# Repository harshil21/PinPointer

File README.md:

View this project on [CADLAB.io](https://cadlab.io/project/29625). 

# PinPointer

This repository will contain all the components which I intend to use for the payload of my rocket. It will include but won't be limited to:

1) Original KiCAD designs for integrating Quectel's LC29H (DA) and (BS) GPS RTK modules
2) Custom Antenna(s) research, building, and tuning, for both GPS and radio telemetry to receive RTCM correction messages from my base station to the rocket.
3) CAD design for assembly of the antennas and modules into the rocket.
4) Microcontroller code (exact microcontroller TBD) which will communicate with an accelerometer (TBD), the GPS module, and a LoRA module (TBD) to transmit and receive at the 915 MHz ISM band.
5) Openrocket file

Primary goals:
1) Scientific curiosity to compare very accurate GPS altitude with pressure altitude.
2) Package and integrate electronics tightly to minimize cost while at the same time have high performance and portability across different rockets. deliberate design decisions.
3) Pave the way for more experimental flights, e.g. active roll control, rocket landings, etc.

Each section will contain how-to's and thought processes. This data will be free and public to everyone who would also like to do the same and iterate.

🚀📡🛰️

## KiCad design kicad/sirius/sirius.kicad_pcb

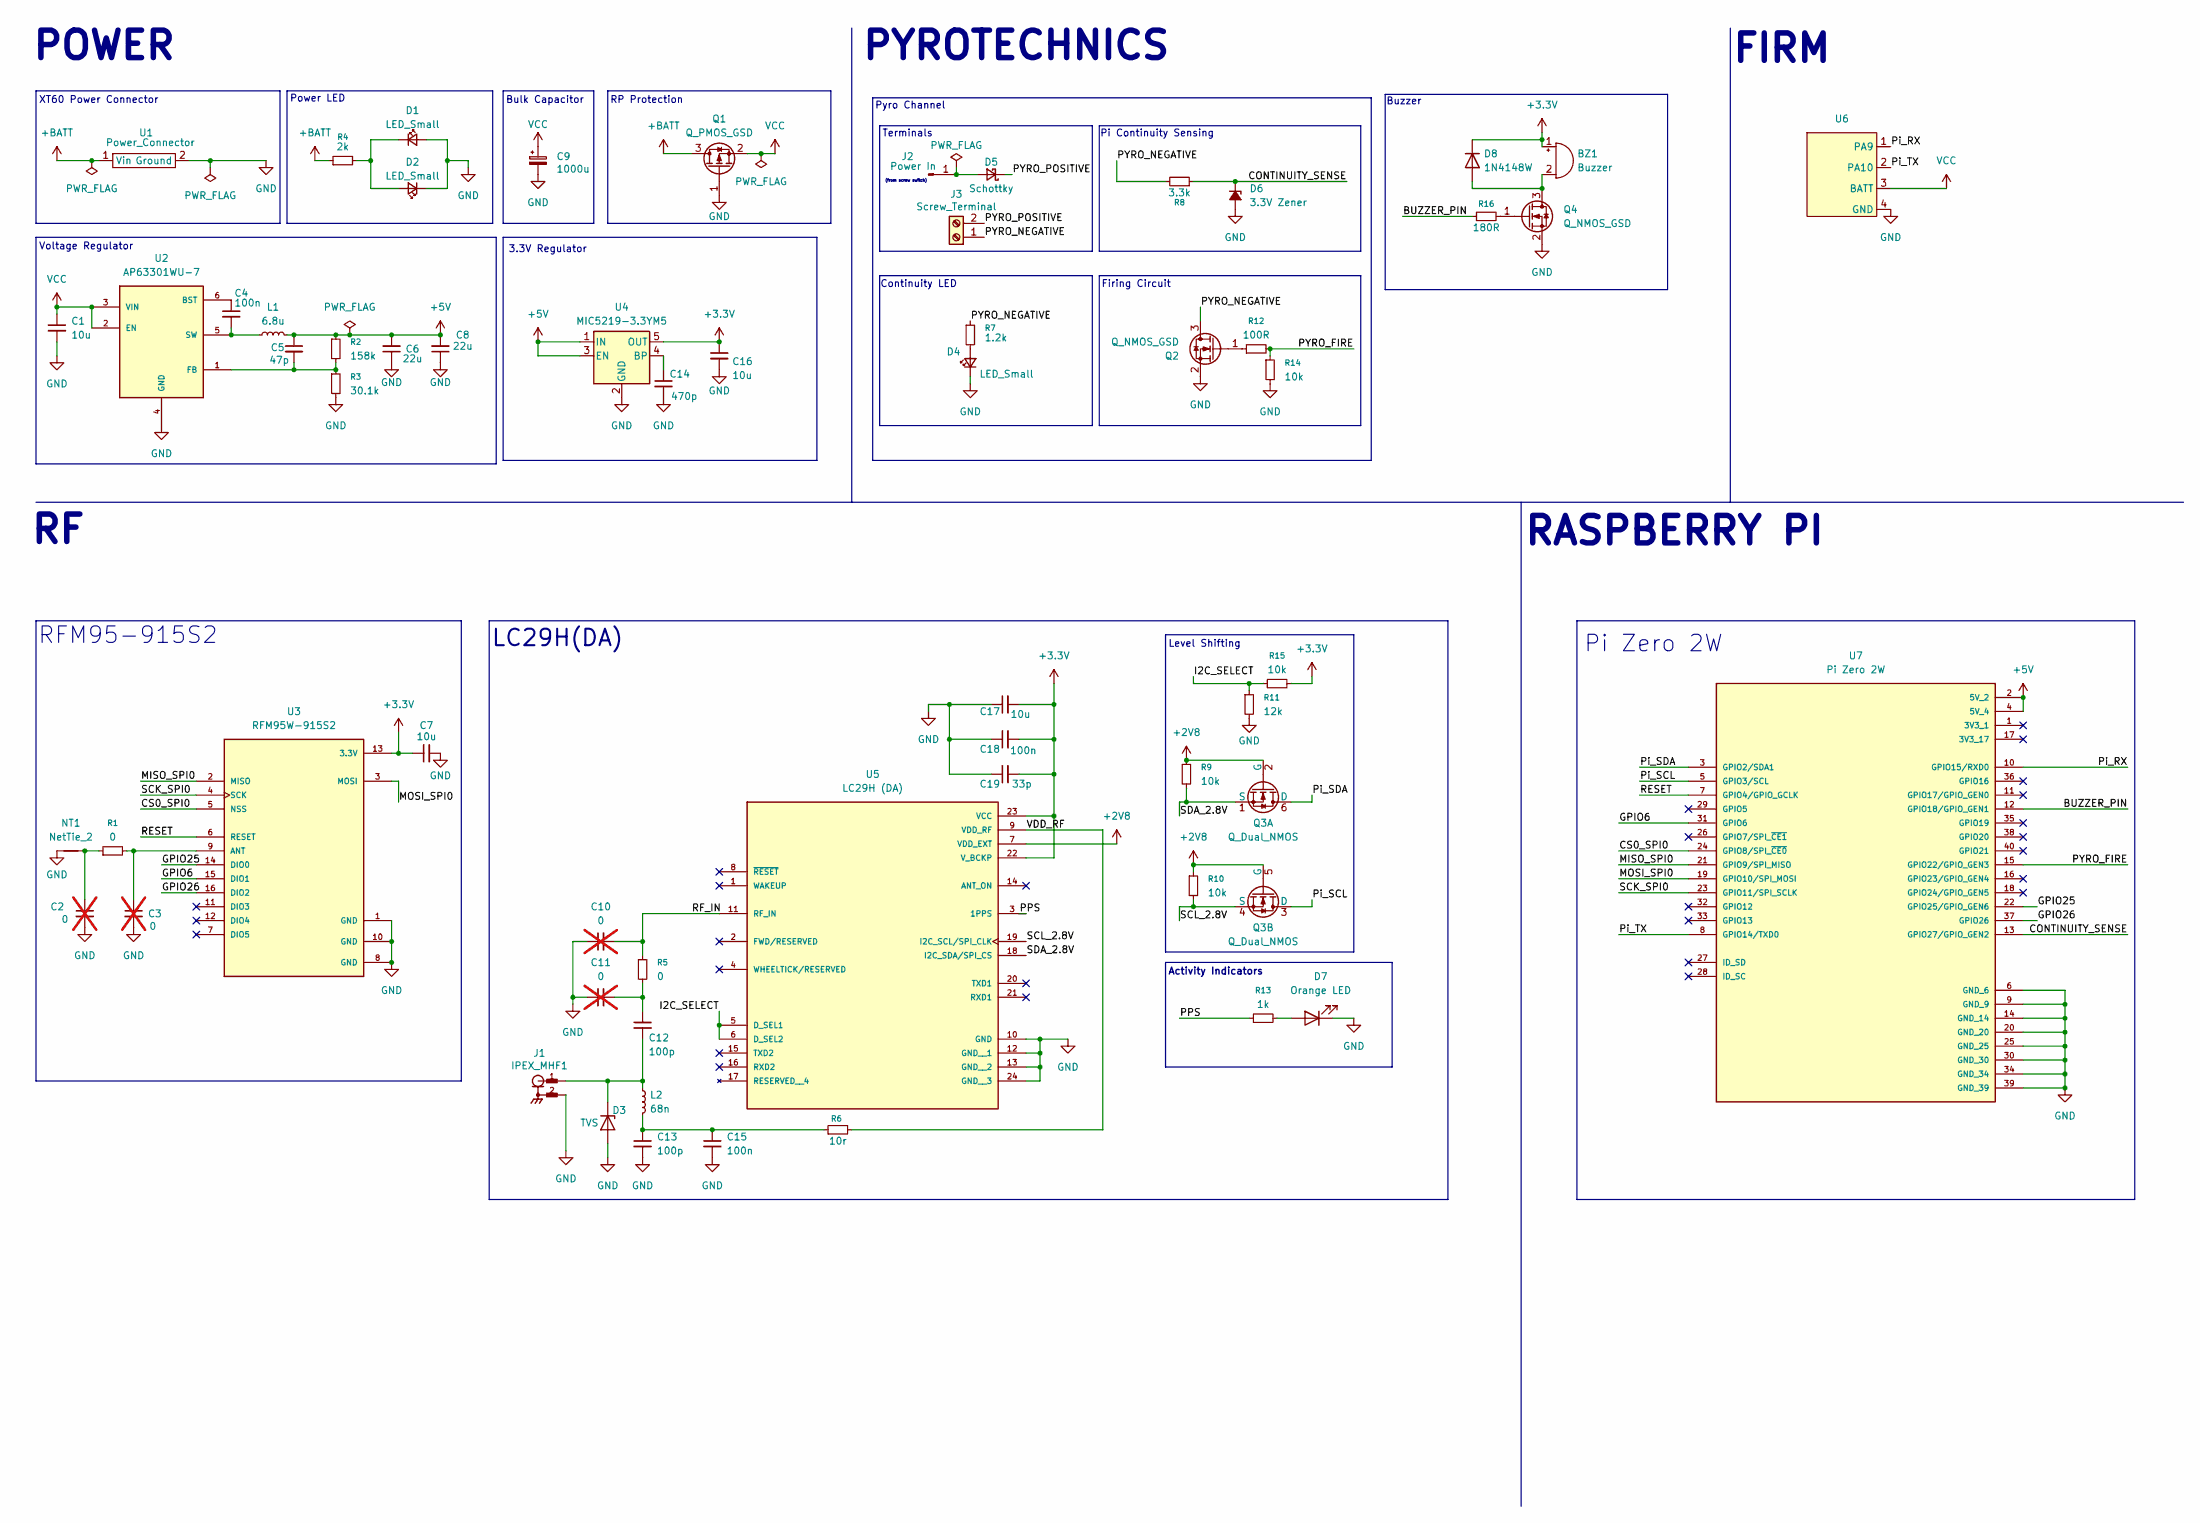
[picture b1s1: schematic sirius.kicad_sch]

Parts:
BZ1: Buzzer; CSS0575ASMTTR; Digikey PN 102-2201-1-ND
C1, C7, C16, C17: 10u; C_0603_1608Metric; Digikey PN 587-3258-1-ND
C2, C3: 0; C_0603_1608Metric; not fitted
C4, C18: 100n; C_0603_1608Metric; Digikey PN 399-C0603C104K3RACTUCT-ND
C5: 47p; C_0603_1608Metric; Digikey PN 1276-1037-1-ND
C6, C8: 22u; C_0603_1608Metric; Digikey PN 490-GRM188R60J226MEA0JCT-ND
C9: 1000u; CP_Elec_10x10.5; Digikey PN 565-HHXJ160ARA102MJC5GCT-ND
C10, C11: 0; C_0402_1005Metric_Pad0.74x0.62mm_HandSolder; not fitted
C12, C13: 100p; C_0402_1005Metric_Pad0.74x0.62mm_HandSolder; Digikey PN 399-C0402C101J5GACTUCT-ND
C14: 470p; C_0603_1608Metric; Digikey PN 1276-1168-1-ND
C15: 100n; C_0402_1005Metric_Pad0.74x0.62mm_HandSolder; Digikey PN 1276-1002-1-ND
C19: 33p; C_0603_1608Metric; Digikey PN 1276-1070-1-ND
D1, D4: LED_Small; LED_0603_1608Metric_Pad1.05x0.95mm_HandSolder; Digikey PN LS Q976.01-N1Q2-1-20-R18
D2: LED_Small; LED_0603_1608Metric_Pad1.05x0.95mm_HandSolder; Digikey PN LTST-C190GKT
D3: TVS; D_SOD-882; Digikey PN F9320CT-ND
D5: Schottky; SOD-323HEUS2H_TOS; Digikey PN 264-CUHS20S60,H3FCT-ND
D6: 3.3V Zener; SOT-23-3; Digikey PN BZX84C3V3LT1GOSCT-ND
D7: Orange LED; LED_0603_1608Metric_Pad1.05x0.95mm_HandSolder; Digikey PN 350-5990030137FCT-ND
D8: 1N4148W; D_SOD-123; Digikey PN 1N4148WSRRGCT-ND
J1: IPEX_MHF1; TE_CONMHF1-SMD-T; Digikey PN 343-CONMHF1-SMD-TCT-ND
J2: Power In; PinHeader_1x01_P2.54mm_Vertical
J3: Screw_Terminal; PinHeader_1x02_P2.54mm_Vertical
L1: 6.8u; 1277AS-H-1R0M=P2; Digikey PN 490-10595-1-ND
L2: 68n; L_0402_1005Metric_Pad0.77x0.64mm_HandSolder; Digikey PN 553-BSCH0010050568NJCPCT-ND
NT1: NetTie_2; IFA_915
Q1: Q_PMOS_GSD; SOT_7DS-T1-GE3_VIS; Digikey PN si2347ds-t1-ge3
Q2, Q4: Q_NMOS_GSD; TSOT-23; Digikey PN 31-DMN2058U-13CT-ND
Q3: Q_Dual_NMOS; SOT-363_SC-70-6; Digikey PN 31-BSS138DWK-13CT-ND
R1: 0; R_0603_1608Metric; Digikey PN 311-0.0GRCT-ND
R2: 158k; R_0603_1608Metric; Digikey PN 311-158KHRCT-ND
R3: 30.1k; R_0603_1608Metric; Digikey PN RMCF0603FT30K1CT-ND
R4: 2k; R_0603_1608Metric; Digikey PN ERJ-PA3J202V
R5: 0; R_0402_1005Metric_Pad0.72x0.64mm_HandSolder; Digikey PN 311-0.0JRCT-ND
R6: 10r; R_0402_1005Metric_Pad0.72x0.64mm_HandSolder; Digikey PN 541-10.0LCT-ND
R7: 1.2k; R_0603_1608Metric; Digikey PN 311-1.20KHRCT-ND
R8: 3.3k; R_0603_1608Metric; Digikey PN 311-3.30KHRCT-ND
R9, R10, R14, R15: 10k; R_0603_1608Metric; Digikey PN 311-10.0KHRCT-ND
R11: 12k; R_0603_1608Metric; Digikey PN P12KDBCT-ND
R12: 100R; R_0603_1608Metric; Digikey PN 311-100HRCT-ND
R13: 1k; R_0603_1608Metric; Digikey PN RMCF0603FT1K00CT-ND
R16: 180R; R_0603_1608Metric; Digikey PN A129679CT-ND
U1: Power_Connector; XT60
U2: AP63301WU-7; SOT95P280X100-6N; Digikey PN 31-AP63301WU-7CT-ND
U3: RFM95W-915S2
U4: MIC5219-3.3YM5; SOT-23-5; MPN C5370977; Digikey PN 576-1281-1-ND
U5: LC29H (DA); LC29H; Digikey PN 2958-LC29HDAMDCT-ND
U6: FIRM v1.0
U7: Pi Zero 2W; Pi_hat_generic

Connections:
+2V8: Q3.2 (G), Q3.5 (G), R9.1, R10.1, U5.7 (VDD_EXT)
+3.3V: BZ1.1 (+), C7.1, C16.1, C17.2, C18.2, C19.2, D8.1 (K), R15.2, U3.13 (3.3V), U4.5 (OUT), U5.22 (V_BCKP), U5.23 (VCC)
+5V: C5.1, C6.2, C8.2, L1.2, R2.1, U4.1 (IN), U4.3 (EN), U7.2 (5V_2), U7.4 (5V_4)
+BATT: Q1.3 (D), R4.1, U1.1 (Vin)
/BUZZER_PIN: R16.1, U7.12 (GPIO18/GPIO_GEN1)
/CONTINUITY_SENSE: D6.3 (K), R8.1, U7.13 (GPIO27/GPIO_GEN2)
/CS0_SPI0: U3.5 (NSS), U7.24 (GPIO8/SPI_~CE0)
/GPIO6: U3.15 (DIO1), U7.31 (GPIO6)
/GPIO25: U3.14 (DIO0), U7.22 (GPIO25/GPIO_GEN6)
/GPIO26: U3.16 (DIO2), U7.37 (GPIO26)
/I2C_SELECT: R11.1, R15.1, U5.5 (D_SEL1), U5.6 (D_SEL2)
/MISO_SPI0: U3.2 (MISO), U7.21 (GPIO9/SPI_MISO)
/MOSI_SPI0: U3.3 (MOSI), U7.19 (GPIO10/SPI_MOSI)
/PPS: R13.1, U5.3 (1PPS)
/PYRO_FIRE: R12.2, R14.1, U7.15 (GPIO22/GPIO_GEN3)
/PYRO_NEGATIVE: J3.1, Q2.3 (D), R7.1, R8.2
/PYRO_POSITIVE: D5.1 (K), J3.2
/Pi_RX: U6.1 (PA9), U7.10 (GPIO15/RXD0)
/Pi_SCL: Q3.3 (D), U7.5 (GPIO3/SCL)
/Pi_SDA: Q3.6 (D), U7.3 (GPIO2/SDA1)
/Pi_TX: U6.2 (PA10), U7.8 (GPIO14/TXD0)
/RESET: U3.6 (RESET), U7.7 (GPIO4/GPIO_GCLK)
/RF_IN: C10.2, R5.1, U5.11 (RF_IN)
/SCK_SPI0: U3.4 (SCK), U7.23 (GPIO11/SPI_SCLK)
/SCL_2.8V: Q3.4 (S), R10.2, U5.19 (I2C_SCL/SPI_CLK)
/SDA_2.8V: Q3.1 (S), R9.2, U5.18 (I2C_SDA/SPI_CS)
/VDD_RF: R6.2, U5.9 (VDD_RF)
GND: C1.2, C2.2, C3.2, C6.1, C7.2, C8.1, C9.2, C10.1, C11.1, C13.2, C14.2, C15.2, C16.2, C17.1, C18.1, C19.1, D1.2 (A), D2.1 (K), D3.2 (A), D4.1 (K), D6.1 (A), D7.1 (K), J1.2, J1.3, J1.4, NT1.1, Q1.1 (G), Q2.2 (S), Q4.2 (S), R3.2, R11.2, R14.2, U1.2 (Ground), U2.4 (GND), U3.1 (GND), U3.8 (GND), U3.10 (GND), U4.2 (GND), U5.10 (GND), U5.12 (GND__1), U5.13 (GND__2), U5.24 (GND__3), U6.4 (GND), U7.6 (GND_6), U7.9 (GND_9), U7.14 (GND_14), U7.20 (GND_20), U7.25 (GND_25), U7.30 (GND_30), U7.34 (GND_34), U7.39 (GND_39)
unnamed: BZ1.2 (-), D8.2 (A), Q4.3 (D)
unnamed: C2.1, NT1.2, R1.1
unnamed: C11.2, C12.1, R5.2
unnamed: C13.1, C15.1, L2.2, R6.1
unnamed: D1.1 (K), D2.2 (A), R4.2
unnamed: C12.2, D3.1 (K), J1.1, L2.1
unnamed: D4.2 (A), R7.2
unnamed: D5.2 (A), J2.1 (Pin_1_1)
unnamed: D7.2 (A), R13.2
unnamed: Q2.1 (G), R12.1
unnamed: Q4.1 (G), R16.2
unnamed: C4.1, U2.6 (BST)
unnamed: C5.2, R2.2, R3.1, U2.1 (FB)
unnamed: C4.2, L1.1, U2.5 (SW)
unnamed: C3.1, R1.2, U3.9 (ANT)
unnamed: C14.1, U4.4 (BP)
VCC: C1.1, C9.1, Q1.2 (S), U2.2 (EN), U2.3 (VIN), U6.3 (BATT)

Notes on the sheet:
LC29H(DA)
Pi Continuity Sensing
Bulk Capacitor
3.3V Regulator
Continuity LED
Firing Circuit
POWER
(from screw switch)
Activity Indicators
RASPBERRY PI
Pyro Channel
RFM95-915S2
XT60 Power Connector
Pi Zero 2W
Buzzer
Power LED
FIRM
Terminals
Voltage Regulator
PYROTECHNICS
Level Shifting
RP Protection

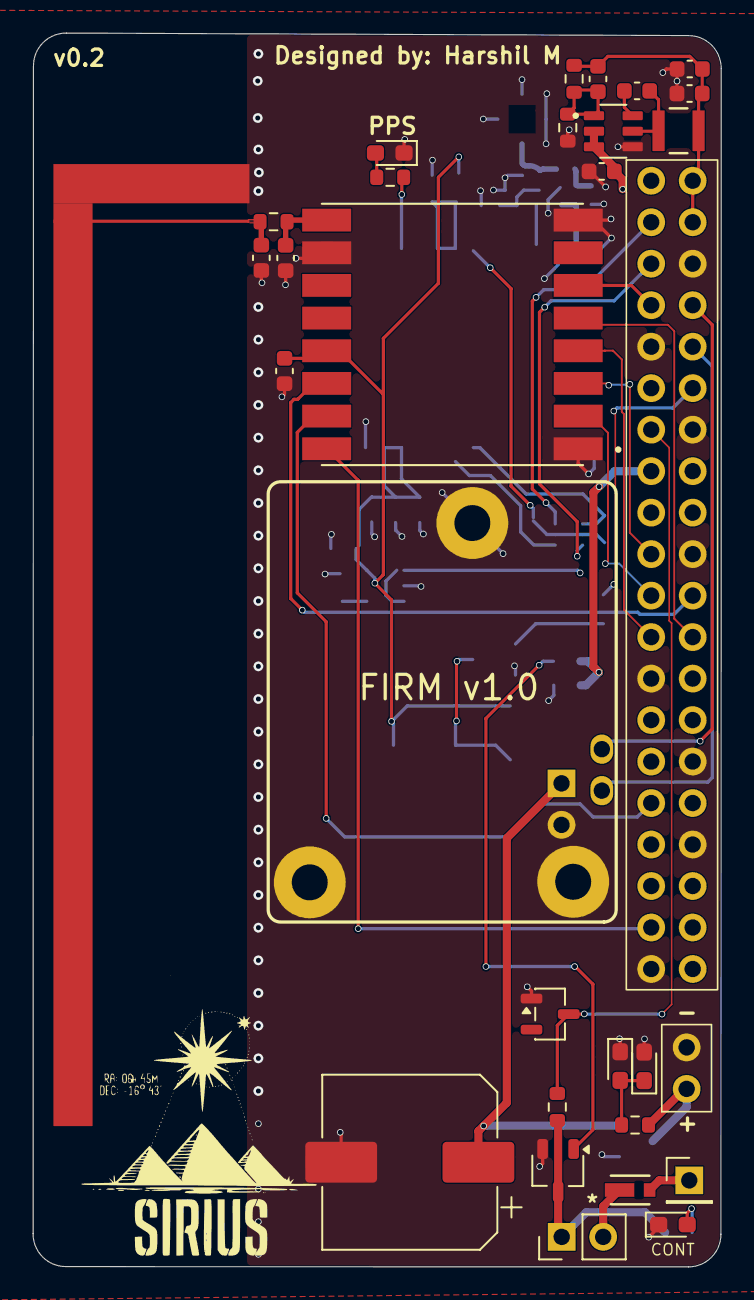
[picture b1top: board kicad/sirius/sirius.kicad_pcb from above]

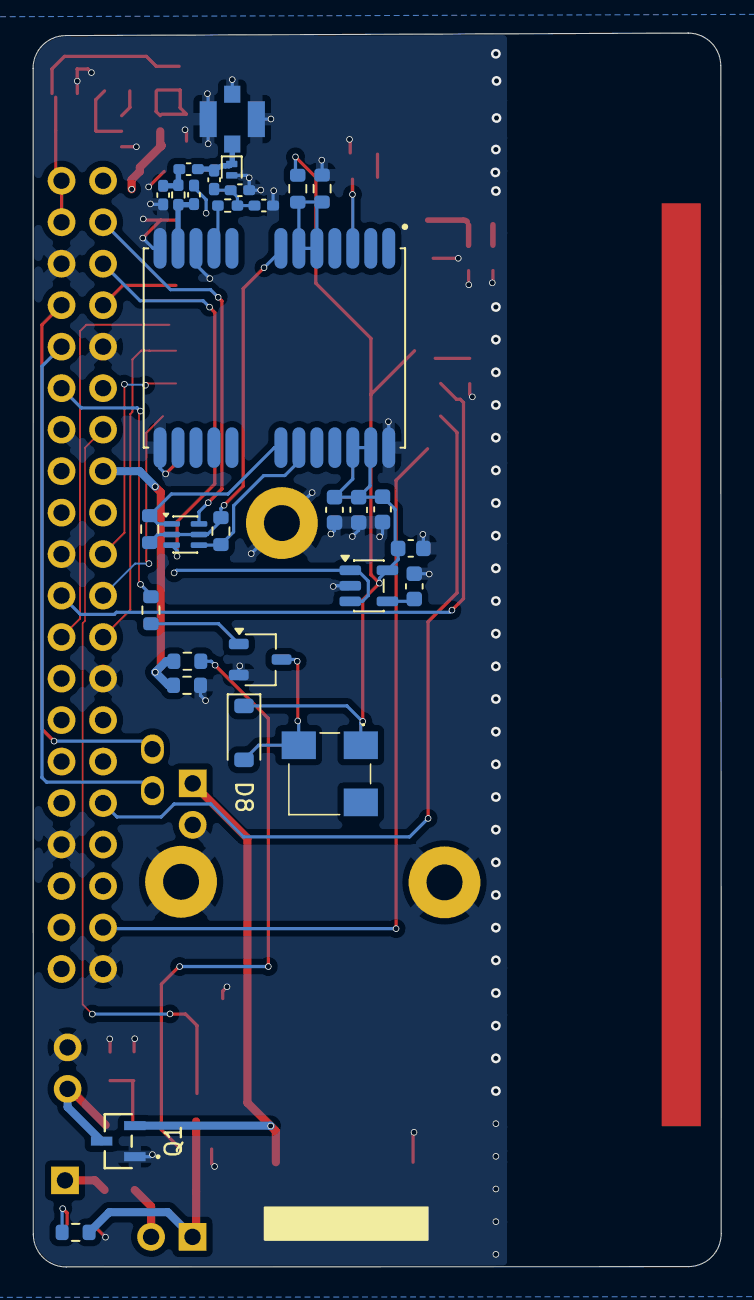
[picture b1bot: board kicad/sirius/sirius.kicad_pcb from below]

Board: 4 copper layers, 42.1 x 75.5 mm, 61 parts (30 on the bottom side), 45 nets.

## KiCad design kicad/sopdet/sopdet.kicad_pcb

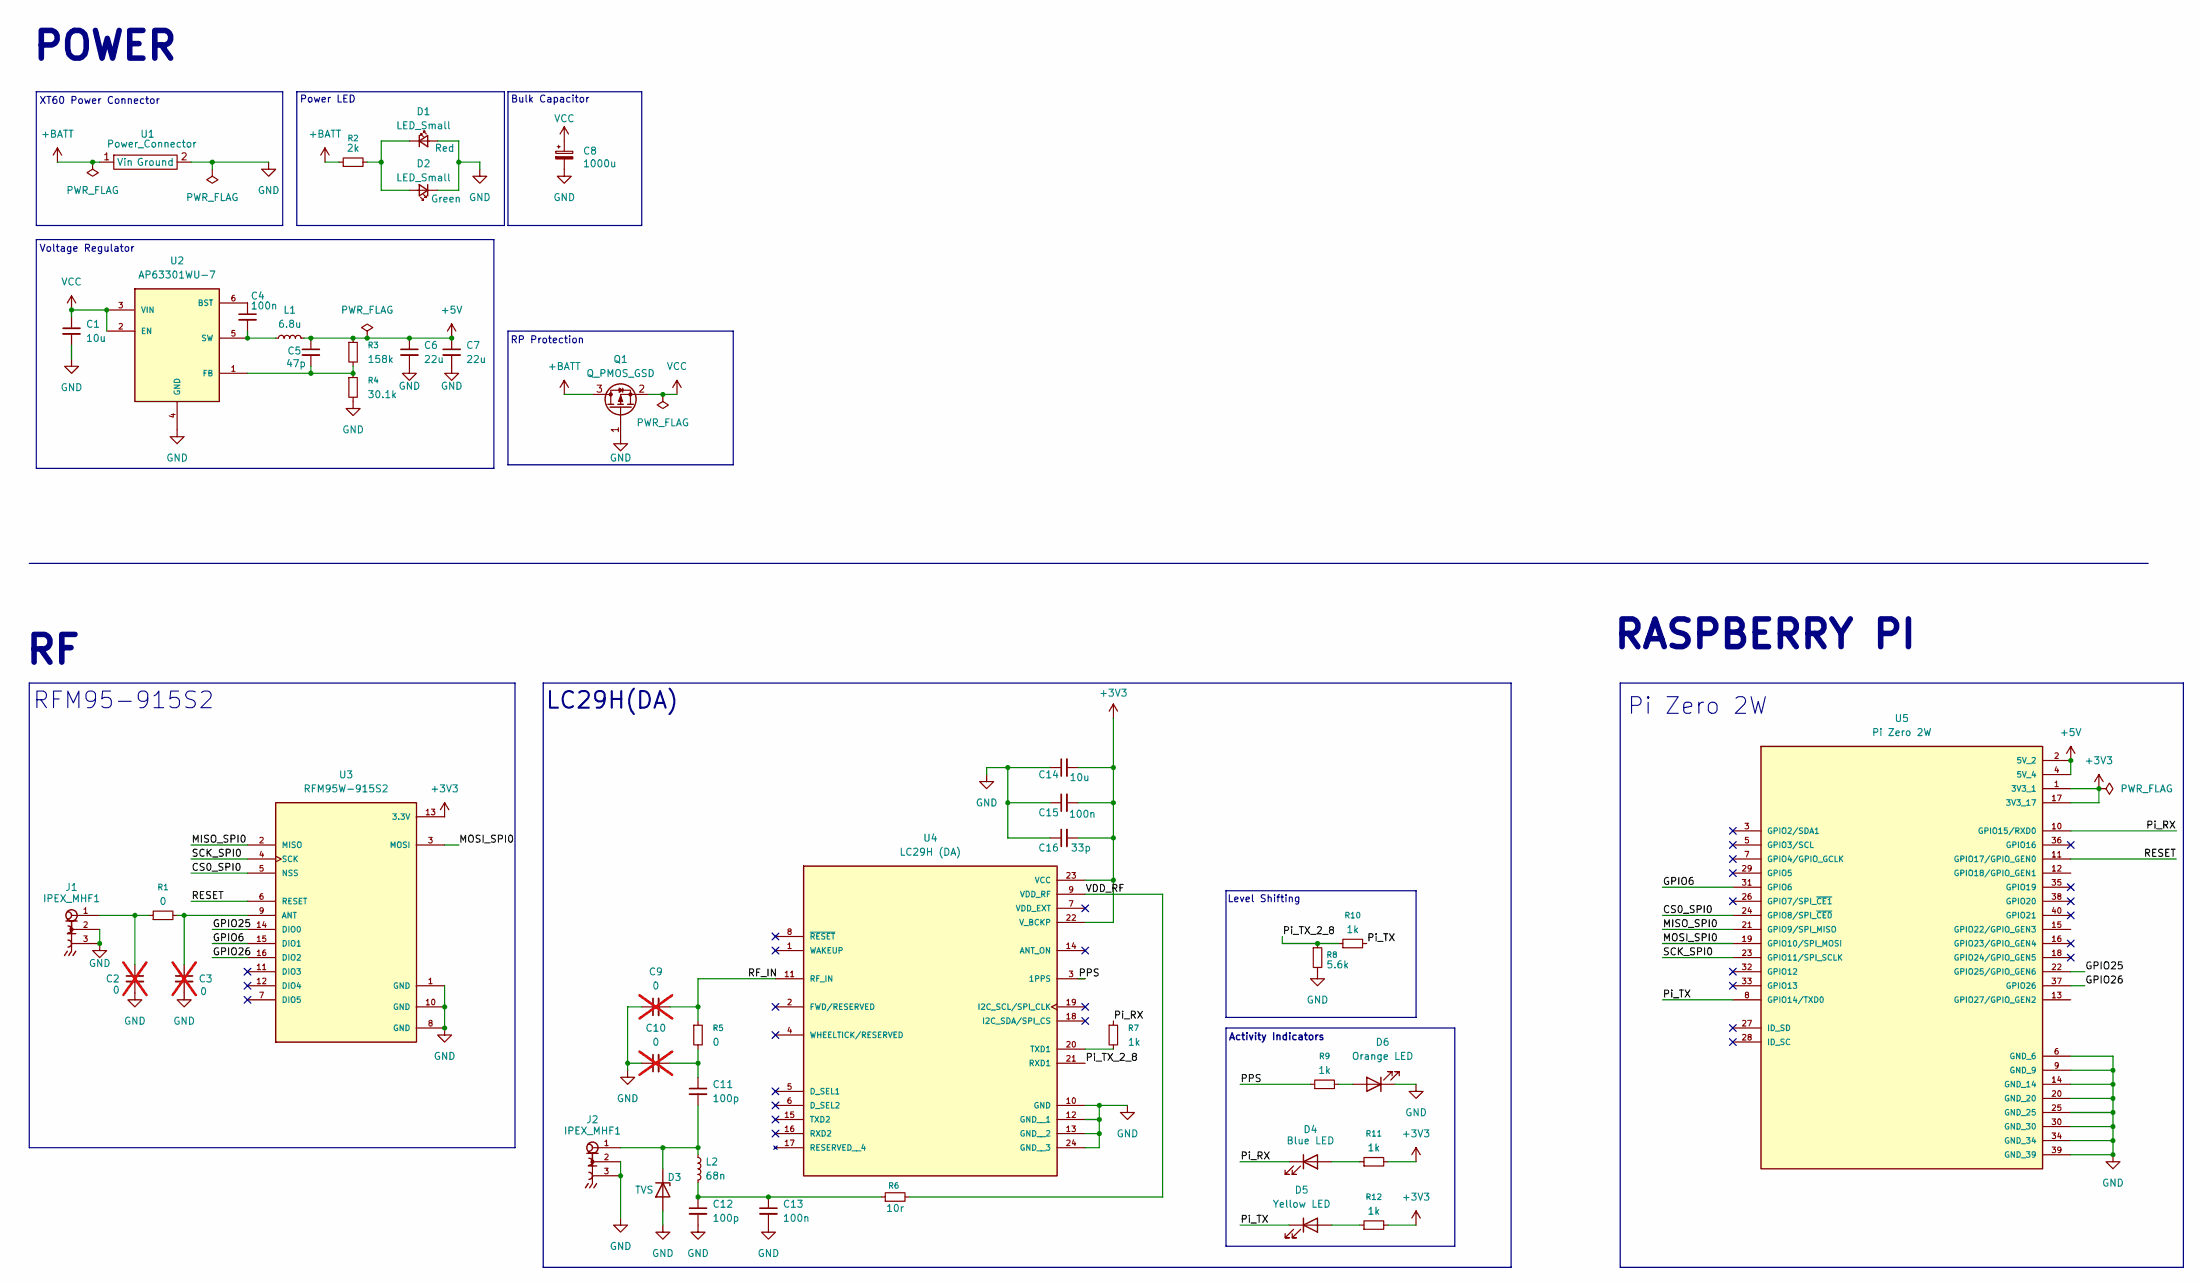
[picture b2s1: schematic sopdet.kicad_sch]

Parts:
C1: 10u; C_0603_1608Metric_Pad1.08x0.95mm_HandSolder
C2, C3, C9, C10: 0; C_0603_1608Metric; not fitted
C4: 100n; C_0603_1608Metric_Pad1.08x0.95mm_HandSolder
C5: 47p; C_0603_1608Metric_Pad1.08x0.95mm_HandSolder
C6, C7: 22u; C_1206_3216Metric
C8: 1000u; CP_Elec_10x10.5
C11, C12: 100p; C_0603_1608Metric
C13, C15: 100n; C_0603_1608Metric
C14: 10u; C_0603_1608Metric
C16: 33p; C_0603_1608Metric
D1: LED_Small; LED_0603_1608Metric_Pad1.05x0.95mm_HandSolder; Digikey PN LS Q976.01-N1Q2-1-20-R18
D2: LED_Small; LED_0603_1608Metric_Pad1.05x0.95mm_HandSolder; Digikey PN LTST-C190GKT
D3: TVS; D_SOD-882; Digikey PN F9320CT-ND
D4: Blue LED; LED_0603_1608Metric_Pad1.05x0.95mm_HandSolder; Digikey PN LTST-C194TBKT
D5: Yellow LED; LED_0603_1608Metric_Pad1.05x0.95mm_HandSolder; Digikey PN 404-1273-1-ND
D6: Orange LED; LED_0603_1608Metric_Pad1.05x0.95mm_HandSolder; Digikey PN 350-5990030137FCT-ND
J1, J2: IPEX_MHF1; ipex_mhf1
L1: 6.8u; 1277AS-H-1R0M=P2; Digikey PN 490-10595-1-ND
L2: 68n; L_0603_1608Metric
Q1: Q_PMOS_GSD; SOT_7DS-T1-GE3_VIS; Digikey PN si2347ds-t1-ge3
R1, R5: 0; R_0603_1608Metric
R2: 2k; R_0603_1608Metric_Pad0.98x0.95mm_HandSolder; Digikey PN ERJ-PA3J202V
R3: 158k; R_0603_1608Metric_Pad0.98x0.95mm_HandSolder
R4: 30.1k; R_0603_1608Metric_Pad0.98x0.95mm_HandSolder
R6: 10r; R_0603_1608Metric
R7, R10: 1k; R_0603_1608Metric_Pad0.98x0.95mm_HandSolder
R8: 5.6k; R_0603_1608Metric_Pad0.98x0.95mm_HandSolder
R9, R11, R12: 1k; R_0603_1608Metric
U1: Power_Connector; XT60
U2: AP63301WU-7; SOT95P280X100-6N; Digikey PN 31-AP63301WU-7CT-ND
U3: RFM95W-915S2
U4: LC29H (DA); LC29H
U5: Pi Zero 2W; Pi_hat_generic; PARTREV April 2024

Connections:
+3V3: C14.2, C15.2, C16.2, R11.2, R12.2, U3.13 (3.3V), U4.22 (V_BCKP), U4.23 (VCC), U5.1 (3V3_1), U5.17 (3V3_17)
+5V: C5.1, C6.1, C7.1, L1.2, R3.1, U5.2 (5V_2), U5.4 (5V_4)
+BATT: Q1.3 (D), R2.1, U1.1 (Vin)
/CS0_SPI0: U3.5 (NSS), U5.24 (GPIO8/SPI_~CE0)
/GPIO6: U3.15 (DIO1), U5.31 (GPIO6)
/GPIO25: U3.14 (DIO0), U5.22 (GPIO25/GPIO_GEN6)
/GPIO26: U3.16 (DIO2), U5.37 (GPIO26)
/MISO_SPI0: U3.2 (MISO), U5.21 (GPIO9/SPI_MISO)
/MOSI_SPI0: U3.3 (MOSI), U5.19 (GPIO10/SPI_MOSI)
/PPS: R9.1, U4.3 (1PPS)
/Pi_RX: D4.1 (K), R7.1, U5.10 (GPIO15/RXD0)
/Pi_TX: D5.1 (K), R10.2, U5.8 (GPIO14/TXD0)
/Pi_TX_2_8: R8.1, R10.1, U4.21 (RXD1)
/RESET: U3.6 (RESET), U5.11 (GPIO17/GPIO_GEN0)
/RF_IN: C9.2, R5.1, U4.11 (RF_IN)
/SCK_SPI0: U3.4 (SCK), U5.23 (GPIO11/SPI_SCLK)
/VDD_RF: R6.2, U4.9 (VDD_RF)
GND: C1.2, C2.2, C3.2, C6.2, C7.2, C8.2, C9.1, C10.1, C12.2, C13.2, C14.1, C15.1, C16.1, D1.2 (A), D2.1 (K), D3.2 (A), D6.1 (K), J1.2, J1.3, J1.4, J2.2, J2.3, J2.4, Q1.1 (G), R4.2, R8.2, U1.2 (Ground), U2.4 (GND), U3.1 (GND), U3.8 (GND), U3.10 (GND), U4.10 (GND), U4.12 (GND__1), U4.13 (GND__2), U4.24 (GND__3), U5.6 (GND_6), U5.9 (GND_9), U5.14 (GND_14), U5.20 (GND_20), U5.25 (GND_25), U5.30 (GND_30), U5.34 (GND_34), U5.39 (GND_39)
unnamed: C2.1, J1.1, R1.1
unnamed: C10.2, C11.1, R5.2
unnamed: C12.1, C13.1, L2.2, R6.1
unnamed: D1.1 (K), D2.2 (A), R2.2
unnamed: C11.2, D3.1 (K), J2.1, L2.1
unnamed: D4.2 (A), R11.1
unnamed: D5.2 (A), R12.1
unnamed: D6.2 (A), R9.2
unnamed: C4.1, U2.6 (BST)
unnamed: C5.2, R3.2, R4.1, U2.1 (FB)
unnamed: C4.2, L1.1, U2.5 (SW)
unnamed: C3.1, R1.2, U3.9 (ANT)
unnamed: R7.2, U4.20 (TXD1)
VCC: C1.1, C8.1, Q1.2 (S), U2.2 (EN), U2.3 (VIN)

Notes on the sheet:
Level Shifting
POWER
XT60 Power Connector
Power LED
LC29H(DA)
RASPBERRY PI
RFM95-915S2
RP Protection
Bulk Capacitor
Activity Indicators
Pi Zero 2W
Voltage Regulator

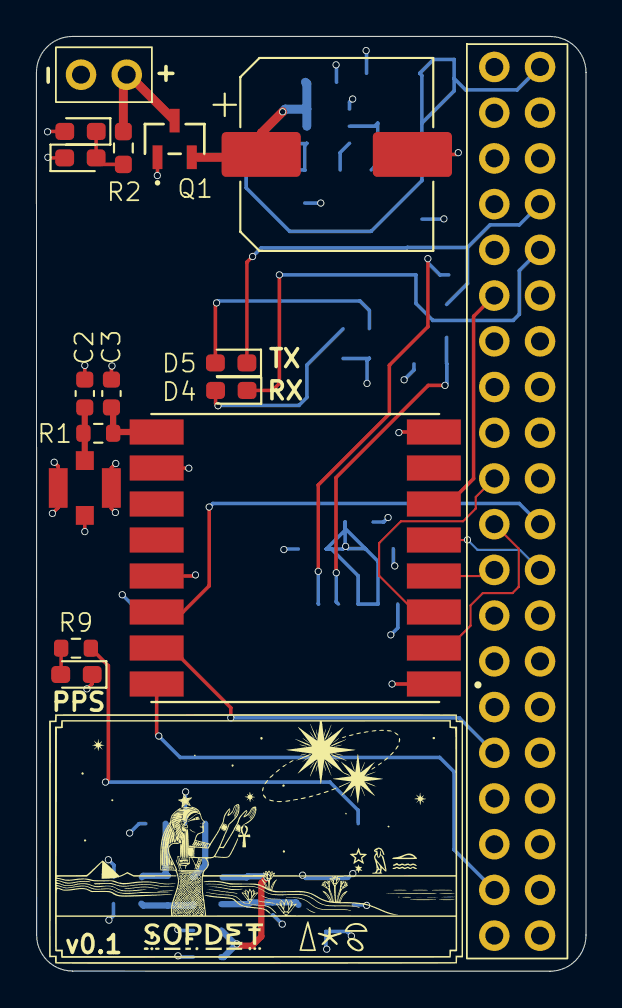
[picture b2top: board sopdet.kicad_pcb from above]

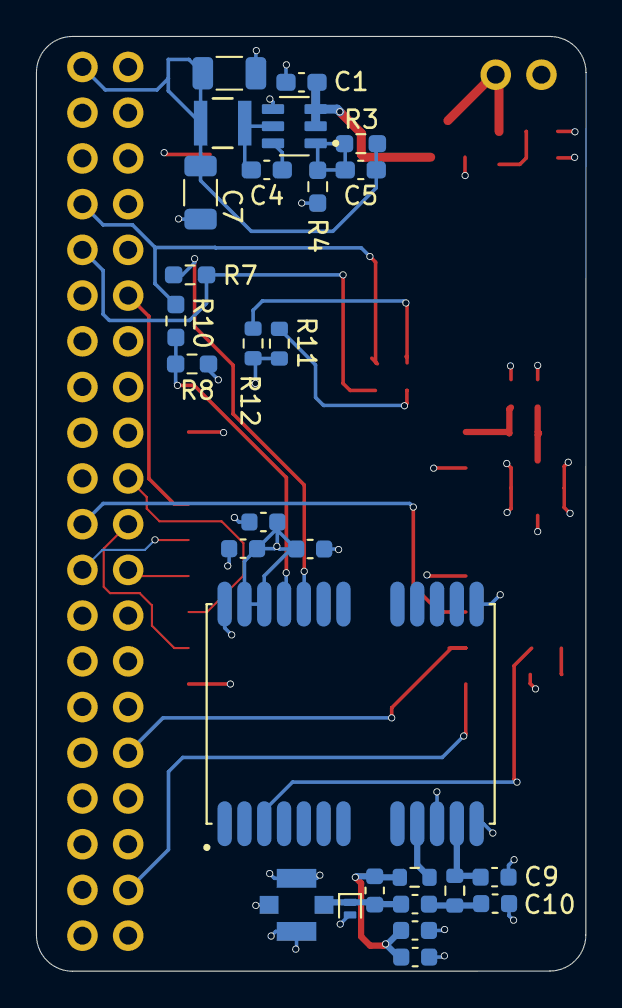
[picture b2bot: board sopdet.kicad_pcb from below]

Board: 4 copper layers, 30.5 x 51.9 mm, 44 parts (28 on the bottom side), 32 nets.

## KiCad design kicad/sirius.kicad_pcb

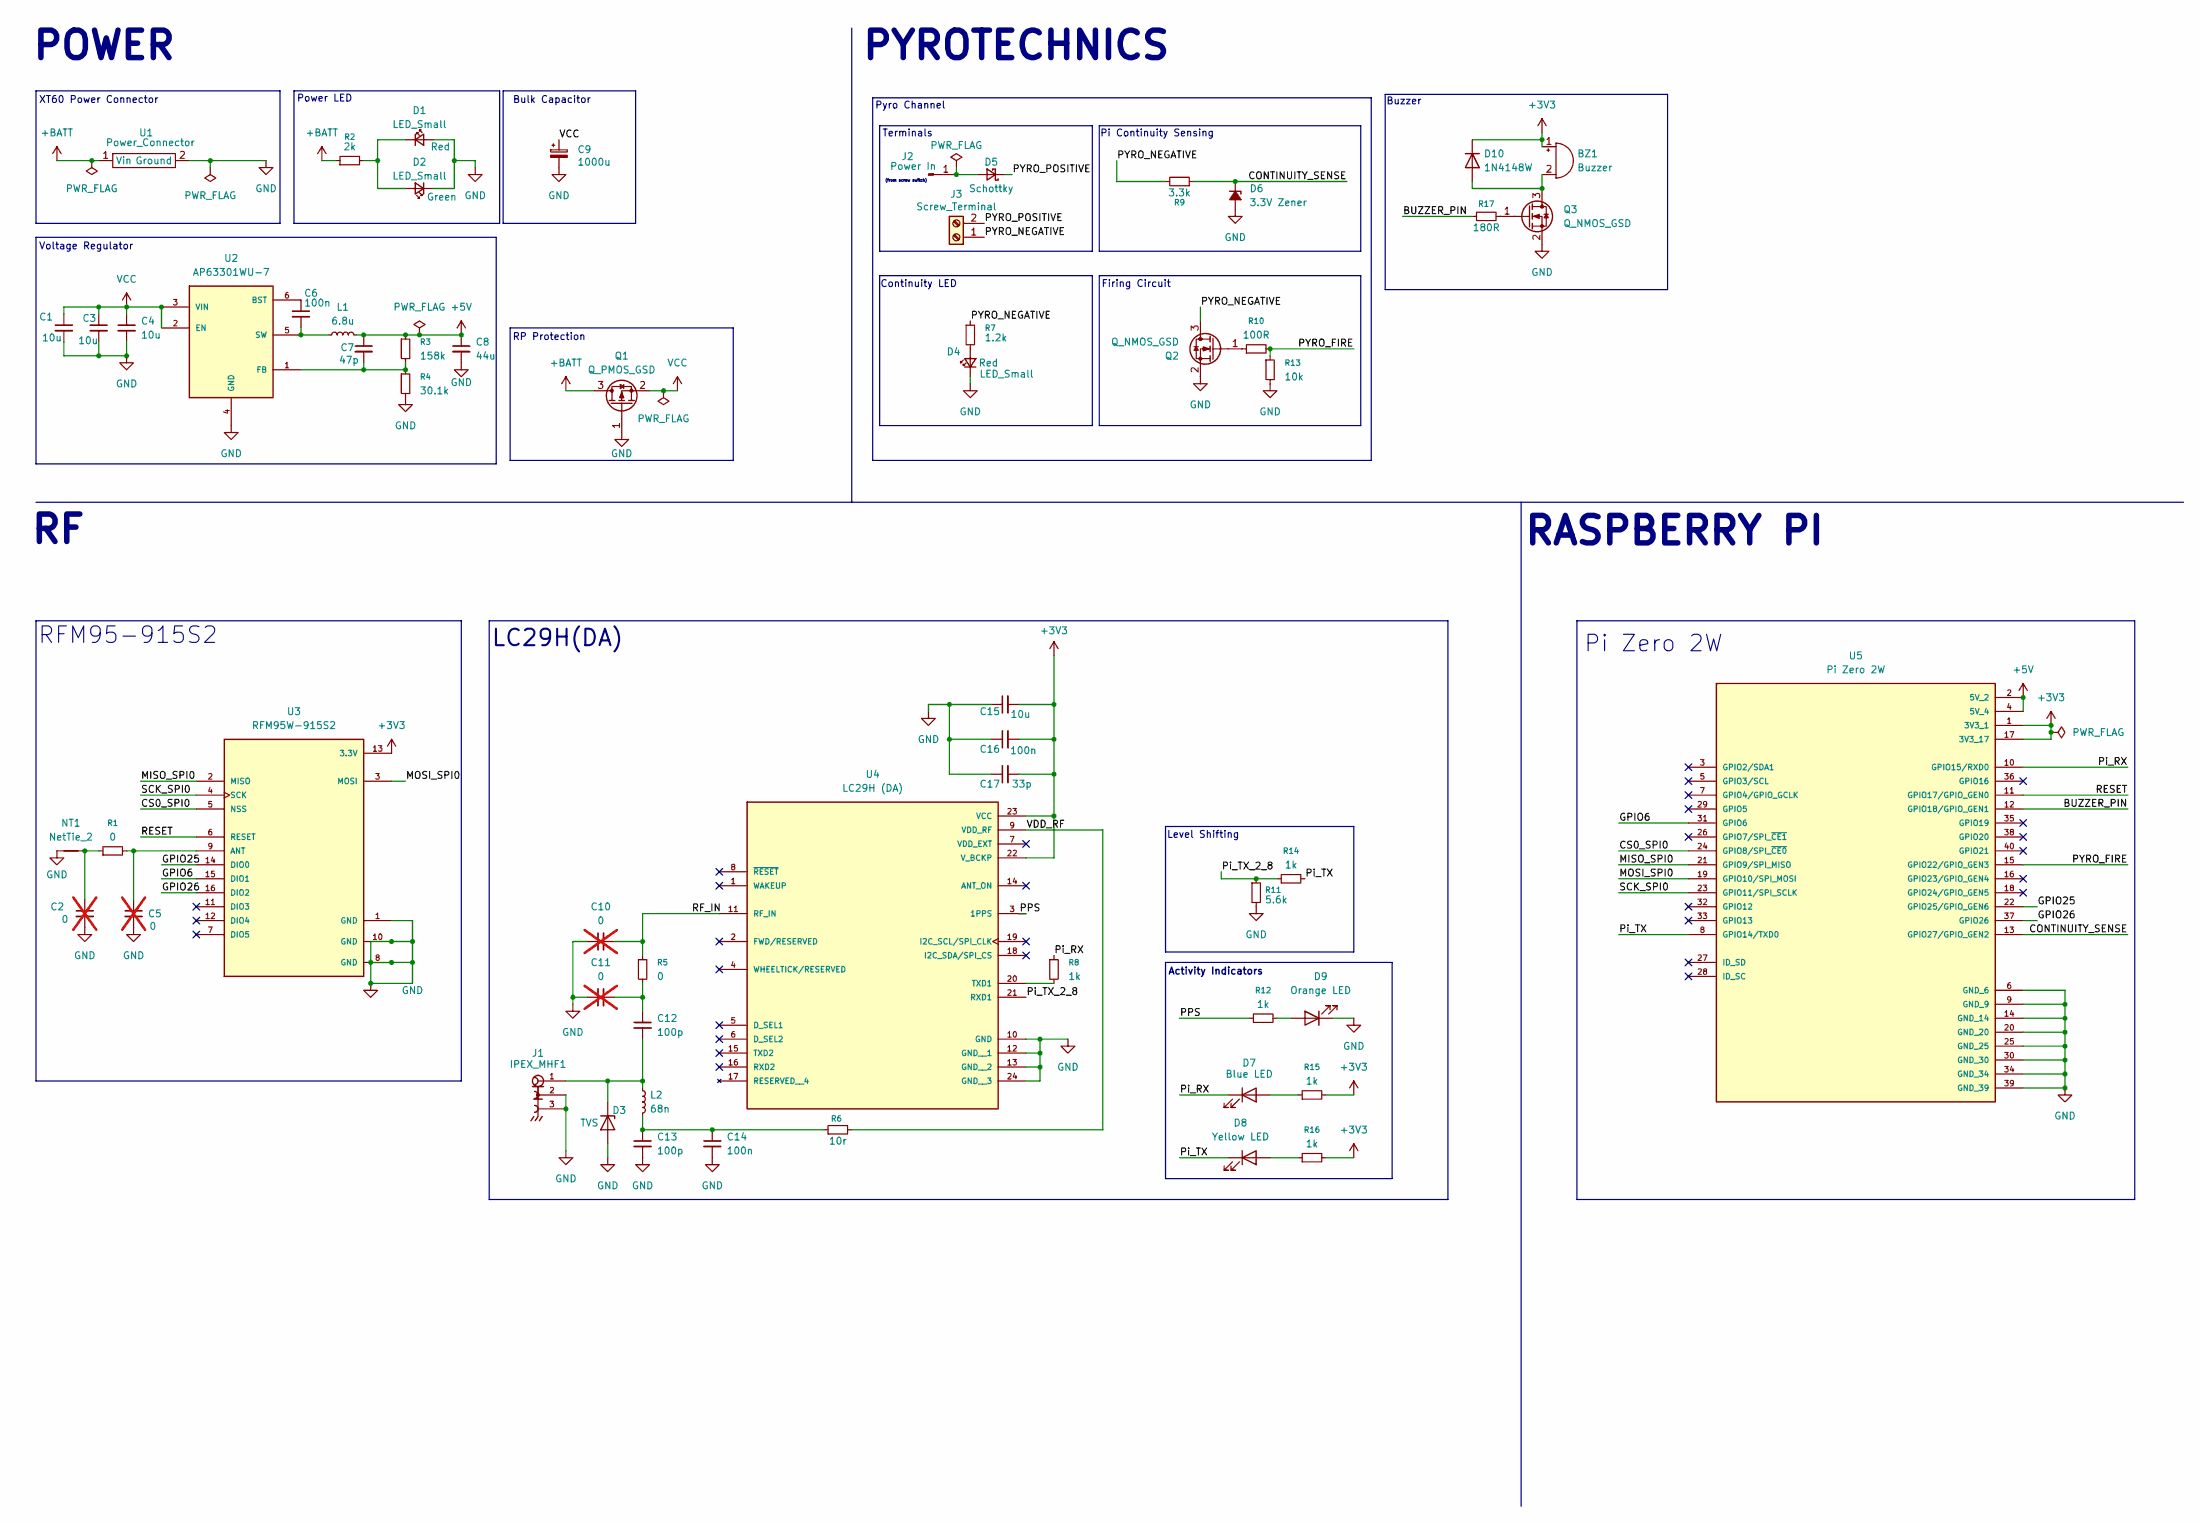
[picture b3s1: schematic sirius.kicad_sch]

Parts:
BZ1: Buzzer; CSS0575ASMTTR; Digikey PN 102-2201-1-ND
C1, C3, C4: 10u; C_0603_1608Metric_Pad1.08x0.95mm_HandSolder
C2, C5, C10, C11: 0; C_0603_1608Metric; not fitted
C6: 100n; C_0603_1608Metric_Pad1.08x0.95mm_HandSolder
C7: 47p; C_0603_1608Metric_Pad1.08x0.95mm_HandSolder
C8: 44u; C_0603_1608Metric_Pad1.08x0.95mm_HandSolder
C9: 1000u; CP_Elec_10x10.5
C12, C13: 100p; C_0603_1608Metric
C14, C16: 100n; C_0603_1608Metric
C15: 10u; C_0603_1608Metric
C17: 33p; C_0603_1608Metric
D1, D4: LED_Small; LED_0603_1608Metric_Pad1.05x0.95mm_HandSolder; Digikey PN LS Q976.01-N1Q2-1-20-R18
D2: LED_Small; LED_0603_1608Metric_Pad1.05x0.95mm_HandSolder; Digikey PN LTST-C190GKT
D3: TVS; D_SOD-882; Digikey PN F9320CT-ND
D5: Schottky; SOD-323HEUS2H_TOS; Digikey PN 264-CUHS20S60,H3FCT-ND
D6: 3.3V Zener; SOT-23-3; Digikey PN BZX84C3V3LT1GOSCT-ND
D7: Blue LED; LED_0603_1608Metric_Pad1.05x0.95mm_HandSolder; Digikey PN LTST-C194TBKT
D8: Yellow LED; LED_0603_1608Metric_Pad1.05x0.95mm_HandSolder; Digikey PN 404-1273-1-ND
D9: Orange LED; LED_0603_1608Metric_Pad1.05x0.95mm_HandSolder; Digikey PN 350-5990030137FCT-ND
D10: 1N4148W; D_SOD-123
J1: IPEX_MHF1; ipex_mhf1
J2: Power In; PinHeader_1x01_P1.00mm_Vertical
J3: Screw_Terminal; TerminalBlock_Phoenix_MPT-0,5-2-2.54_1x02_P2.54mm_Horizontal
L1: 6.8u; 1277AS-H-1R0M=P2; Digikey PN 490-10595-1-ND
L2: 68n; L_0603_1608Metric
NT1: NetTie_2; IFA_915
Q1: Q_PMOS_GSD; SOT_7DS-T1-GE3_VIS; Digikey PN si2347ds-t1-ge3
Q2, Q3: Q_NMOS_GSD; TSOT-23; Digikey PN IRLML2502TRPBFCT-ND
R1, R5: 0; R_0603_1608Metric
R2: 2k; R_0603_1608Metric_Pad0.98x0.95mm_HandSolder; Digikey PN ERJ-PA3J202V
R3: 158k; R_0603_1608Metric_Pad0.98x0.95mm_HandSolder
R4: 30.1k; R_0603_1608Metric_Pad0.98x0.95mm_HandSolder
R6: 10r; R_0603_1608Metric
R7: 1.2k; R_0603_1608Metric_Pad0.98x0.95mm_HandSolder
R8, R14: 1k; R_0603_1608Metric_Pad0.98x0.95mm_HandSolder
R9: 3.3k; R_0603_1608Metric_Pad0.98x0.95mm_HandSolder
R10: 100R; R_0603_1608Metric_Pad0.98x0.95mm_HandSolder
R11: 5.6k; R_0603_1608Metric_Pad0.98x0.95mm_HandSolder
R12, R15, R16: 1k; R_0603_1608Metric
R13: 10k; R_0603_1608Metric_Pad0.98x0.95mm_HandSolder
R17: 180R; R_0603_1608Metric_Pad0.98x0.95mm_HandSolder
U1: Power_Connector; XT60
U2: AP63301WU-7; SOT95P280X100-6N; Digikey PN 31-AP63301WU-7CT-ND
U3: RFM95W-915S2
U4: LC29H (DA); LC29H
U5: Pi Zero 2W; Pi_hat_generic; PARTREV April 2024

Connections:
+3V3: BZ1.1 (+), C15.2, C16.2, C17.2, D10.1 (K), R15.2, R16.2, U3.13 (3.3V), U4.22 (V_BCKP), U4.23 (VCC), U5.1 (3V3_1), U5.17 (3V3_17)
+5V: C7.1, C8.1, L1.2, R3.1, U5.2 (5V_2), U5.4 (5V_4)
+BATT: Q1.3 (D), R2.1, U1.1 (Vin)
/BUZZER_PIN: R17.1, U5.12 (GPIO18/GPIO_GEN1)
/CONTINUITY_SENSE: D6.3 (K), R9.1, U5.13 (GPIO27/GPIO_GEN2)
/CS0_SPI0: U3.5 (NSS), U5.24 (GPIO8/SPI_~CE0)
/GPIO6: U3.15 (DIO1), U5.31 (GPIO6)
/GPIO25: U3.14 (DIO0), U5.22 (GPIO25/GPIO_GEN6)
/GPIO26: U3.16 (DIO2), U5.37 (GPIO26)
/MISO_SPI0: U3.2 (MISO), U5.21 (GPIO9/SPI_MISO)
/MOSI_SPI0: U3.3 (MOSI), U5.19 (GPIO10/SPI_MOSI)
/PPS: R12.1, U4.3 (1PPS)
/PYRO_FIRE: R10.2, R13.1, U5.15 (GPIO22/GPIO_GEN3)
/PYRO_NEGATIVE: J3.1, Q2.3 (D), R7.1, R9.2
/PYRO_POSITIVE: D5.1 (K), J3.2
/Pi_RX: D7.1 (K), R8.1, U5.10 (GPIO15/RXD0)
/Pi_TX: D8.1 (K), R14.2, U5.8 (GPIO14/TXD0)
/Pi_TX_2_8: R11.1, R14.1, U4.21 (RXD1)
/RESET: U3.6 (RESET), U5.11 (GPIO17/GPIO_GEN0)
/RF_IN: C10.2, R5.1, U4.11 (RF_IN)
/SCK_SPI0: U3.4 (SCK), U5.23 (GPIO11/SPI_SCLK)
/VDD_RF: R6.2, U4.9 (VDD_RF)
GND: C1.2, C2.2, C3.2, C4.2, C5.2, C8.2, C9.2, C10.1, C11.1, C13.2, C14.2, C15.1, C16.1, C17.1, D1.2 (A), D2.1 (K), D3.2 (A), D4.1 (K), D6.1 (A), D9.1 (K), J1.2, J1.3, NT1.1, Q1.1 (G), Q2.2 (S), Q3.2 (S), R4.2, R11.2, R13.2, U1.2 (Ground), U2.4 (GND), U3.1 (GND), U3.8 (GND), U3.10 (GND), U4.10 (GND), U4.12 (GND__1), U4.13 (GND__2), U4.24 (GND__3), U5.6 (GND_6), U5.9 (GND_9), U5.14 (GND_14), U5.20 (GND_20), U5.25 (GND_25), U5.30 (GND_30), U5.34 (GND_34), U5.39 (GND_39)
unnamed: BZ1.2 (-), D10.2 (A), Q3.3 (D)
unnamed: C2.1, NT1.2, R1.1
unnamed: C11.2, C12.1, R5.2
unnamed: C13.1, C14.1, L2.2, R6.1
unnamed: D1.1 (K), D2.2 (A), R2.2
unnamed: C12.2, D3.1 (K), J1.1, L2.1
unnamed: D4.2 (A), R7.2
unnamed: D5.2 (A), J2.1 (Pin_1_1)
unnamed: D7.2 (A), R15.1
unnamed: D8.2 (A), R16.1
unnamed: D9.2 (A), R12.2
unnamed: Q2.1 (G), R10.1
unnamed: Q3.1 (G), R17.2
unnamed: C6.1, U2.6 (BST)
unnamed: C7.2, R3.2, R4.1, U2.1 (FB)
unnamed: C6.2, L1.1, U2.5 (SW)
unnamed: C5.1, R1.2, U3.9 (ANT)
unnamed: R8.2, U4.20 (TXD1)
VCC: C1.1, C3.1, C4.1, C9.1, Q1.2 (S), U2.2 (EN), U2.3 (VIN)

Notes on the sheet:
LC29H(DA)
Pi Continuity Sensing
Bulk Capacitor
Continuity LED
Firing Circuit
POWER
(from screw switch)
Activity Indicators
RASPBERRY PI
Pyro Channel
RFM95-915S2
XT60 Power Connector
Pi Zero 2W
Buzzer
Power LED
Terminals
Voltage Regulator
PYROTECHNICS
Level Shifting
RP Protection
